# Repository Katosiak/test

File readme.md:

# System irygacji TytusPro

Aktualnie nasza firma “TytusPro”  zajmuję się realizacją projektu zautomatyzowanego systemu irygacyjnego stosowanego do nawadniania growboxa metodą deszczowania, czyli wytwarzania sztucznego deszczu poprzez deszczownicę. Do naszego urządzenia włączyliśmy 12 voltową pompę wody, oraz system rur aluminiowych. Nie zabrakło również lampy HPS która jest dopasowywana do danego growboxa w zależności od zapotrzebowania na moc (jeśli chodzi o małe pojemniki będzie to 250W). Sam growbox będzie wykonany z kawałków płyty wiórowej oraz listew. Woda jest dostarczana weżykiem do dysza zraszającego. Całe urządzenie funkcjonjuje pod zaprogramowanym zegarem który w zależności od cyklu dnia bądź nocy uruchamia światło jak i mechanizm zraszający naszą roślinę. Po całkowitej integracji urządzenia możesz udać się nawet na długie wakacje pozostawiając roślinę w naszych rękach. TytusPro dbamy o twoją zieleń!

## Plan działania 

# Elementy potrzebne do zbudowania naszego systemu wraz z ich parametrami

1. Pompa Wody
    - zasilanie 12V
    - wężyk o długości min. 150cm
    - średnica wylotu 1cm
    - wysokość podnoszenia wody wystarczy do 2,5/3 metrów
    - ciśnienie od 0,4 do 0,6 Bara

2. Oświetlenie – lampa HPS:
    - zależnie od warunków moc 250W lub 400W (bardziej 250W dla małego growboxa)

3. Wentylator:
    - około 30 wymian powietrza na godzinę
    - zasilanie 12V

4. Gniazdo e40 do lamp HPS

5. Przykładowe wymiary i materiały do budowy growboxa:]
    - 3 kawałki sklejki lub płyty wiórowej o wymiarach  1,21 metra x 2,42 metra i grubości  1,27 cm, przecięte na pół aby uzyskać sześć kawałków o wymiarach 1,21 m) x 1,21 m
    - 6 listew o szerokości 3,8 cm, grubości 3,8 cm i długości 2,43 m

6. Rury aluminiowe:]
    - średnica 1 cm
    - długość rur do 2/3 metrów

7. Kolanka aluminiowe:]
    - średnica 1 cm

8. Kable miedziane 2-żyłowe na napięcie 12V][]

9. Dysza do zraszania
    - średnica 1cm

# Schemat poglądowy systemu iregacyjnego

# Algorytm blokowy

# Opis fragmentów kodu

 - Czas i data uruchomienia

```C
RTC_Datetime_t datetime_start = {         
  .year = 23,
  .month = 02,
  .month_day = 03,                        
  .hour = 16,
  .minute = 00,
  .second = 00
};
```
- Zadeklarowane zdarzenia

```C
typedef enum {                          
	EVENT_Enable_Sun,
	EVENT_Enable_Water,
	EVENT_Enable_Air,
	EVENT_Disable_Sun,
	EVENT_Disable_Water,
	EVENT_Disable_Air,
} Event_e;
```
- Tablica alarmów, którą ustawiamy przed programowaniem urządzenia. Alarmy mają następować po sobie.

```C
 Alarm_t alarm_array[ALARM_COUNT] = {         
		{ .event = EVENT_Enable_Sun, .alarm = { .day_mask = true, .hour = 8, .minute = 0, .second = 0 } },
		{ .event = EVENT_Enable_Air, .alarm = { .day_mask = true, .hour = 12, .minute = 0, .second = 0 } },
		{ .event = EVENT_Enable_Water, .alarm = { .day_mask = true, .hour = 15, .minute = 0, .second = 0 } },
		{ .event = EVENT_Disable_Water, .alarm = { .day_mask = true, .hour = 15, .minute = 3, .second = 0 } },
		{ .event = EVENT_Disable_Air, .alarm = { .day_mask = true, .hour = 18, .minute = 0, .second = 0 } },
		{ .event = EVENT_Disable_Sun, .alarm = { .day_mask = true, .hour = 22, .minute = 0, .second = 0 } }
};
```
- Pętla for sprawdzająca najbliższy alarm z tablicy (NIE DZIAŁA)

```C
 for (uint8_t i = 0; i < ALARM_COUNT; i++) {                
    if(datetime_start.hour >= alarm_array[i].alarm.hour &&
       datetime_start.minute >= alarm_array[i].alarm.minute &&
	   datetime_start.second >= alarm_array[i].alarm.second) {

        RTC_Alarm_A_Enable(&(alarm_array[i].alarm));
 ```
- Event świadczy o obsłudze danego alarmu    

```C
 while(1)
		  {
			if(RTC_Event_A()) {

				switch(alarm_array[alarm_now].event) {         
				  case EVENT_Enable_Sun:
					  //for enable sun
					  break;
				  case EVENT_Enable_Air:
					  //for enable air
					  break;
				  case EVENT_Enable_Water:
					  //for enable water
					  break;
				  case EVENT_Disable_Water:
				  	  //for disable water
					  break;
				  case EVENT_Disable_Air:
					  //for disable air
					  break;
				  case EVENT_Disable_Sun:
					  //for disable sun
				  	  break;

				}
```
- Zwiększamy alarm o jeden, jeżeli nasz alarm jest większy bądź równy to zaczynamy od początku.
```js

				alarm_now++;                      
				if(alarm_now >= ALARM_COUNT) alarm_now = 0;     
				RTC_Alarm_A_Enable(&(alarm_array[alarm_now].alarm));

			  __NOP();
			}
			__NOP();
		  }
		 }

  }
}
```
#  Co należy dodać w przyszłości?

- Poprawić pętle for

- Ustawić pod przyciskiem aktualny czas

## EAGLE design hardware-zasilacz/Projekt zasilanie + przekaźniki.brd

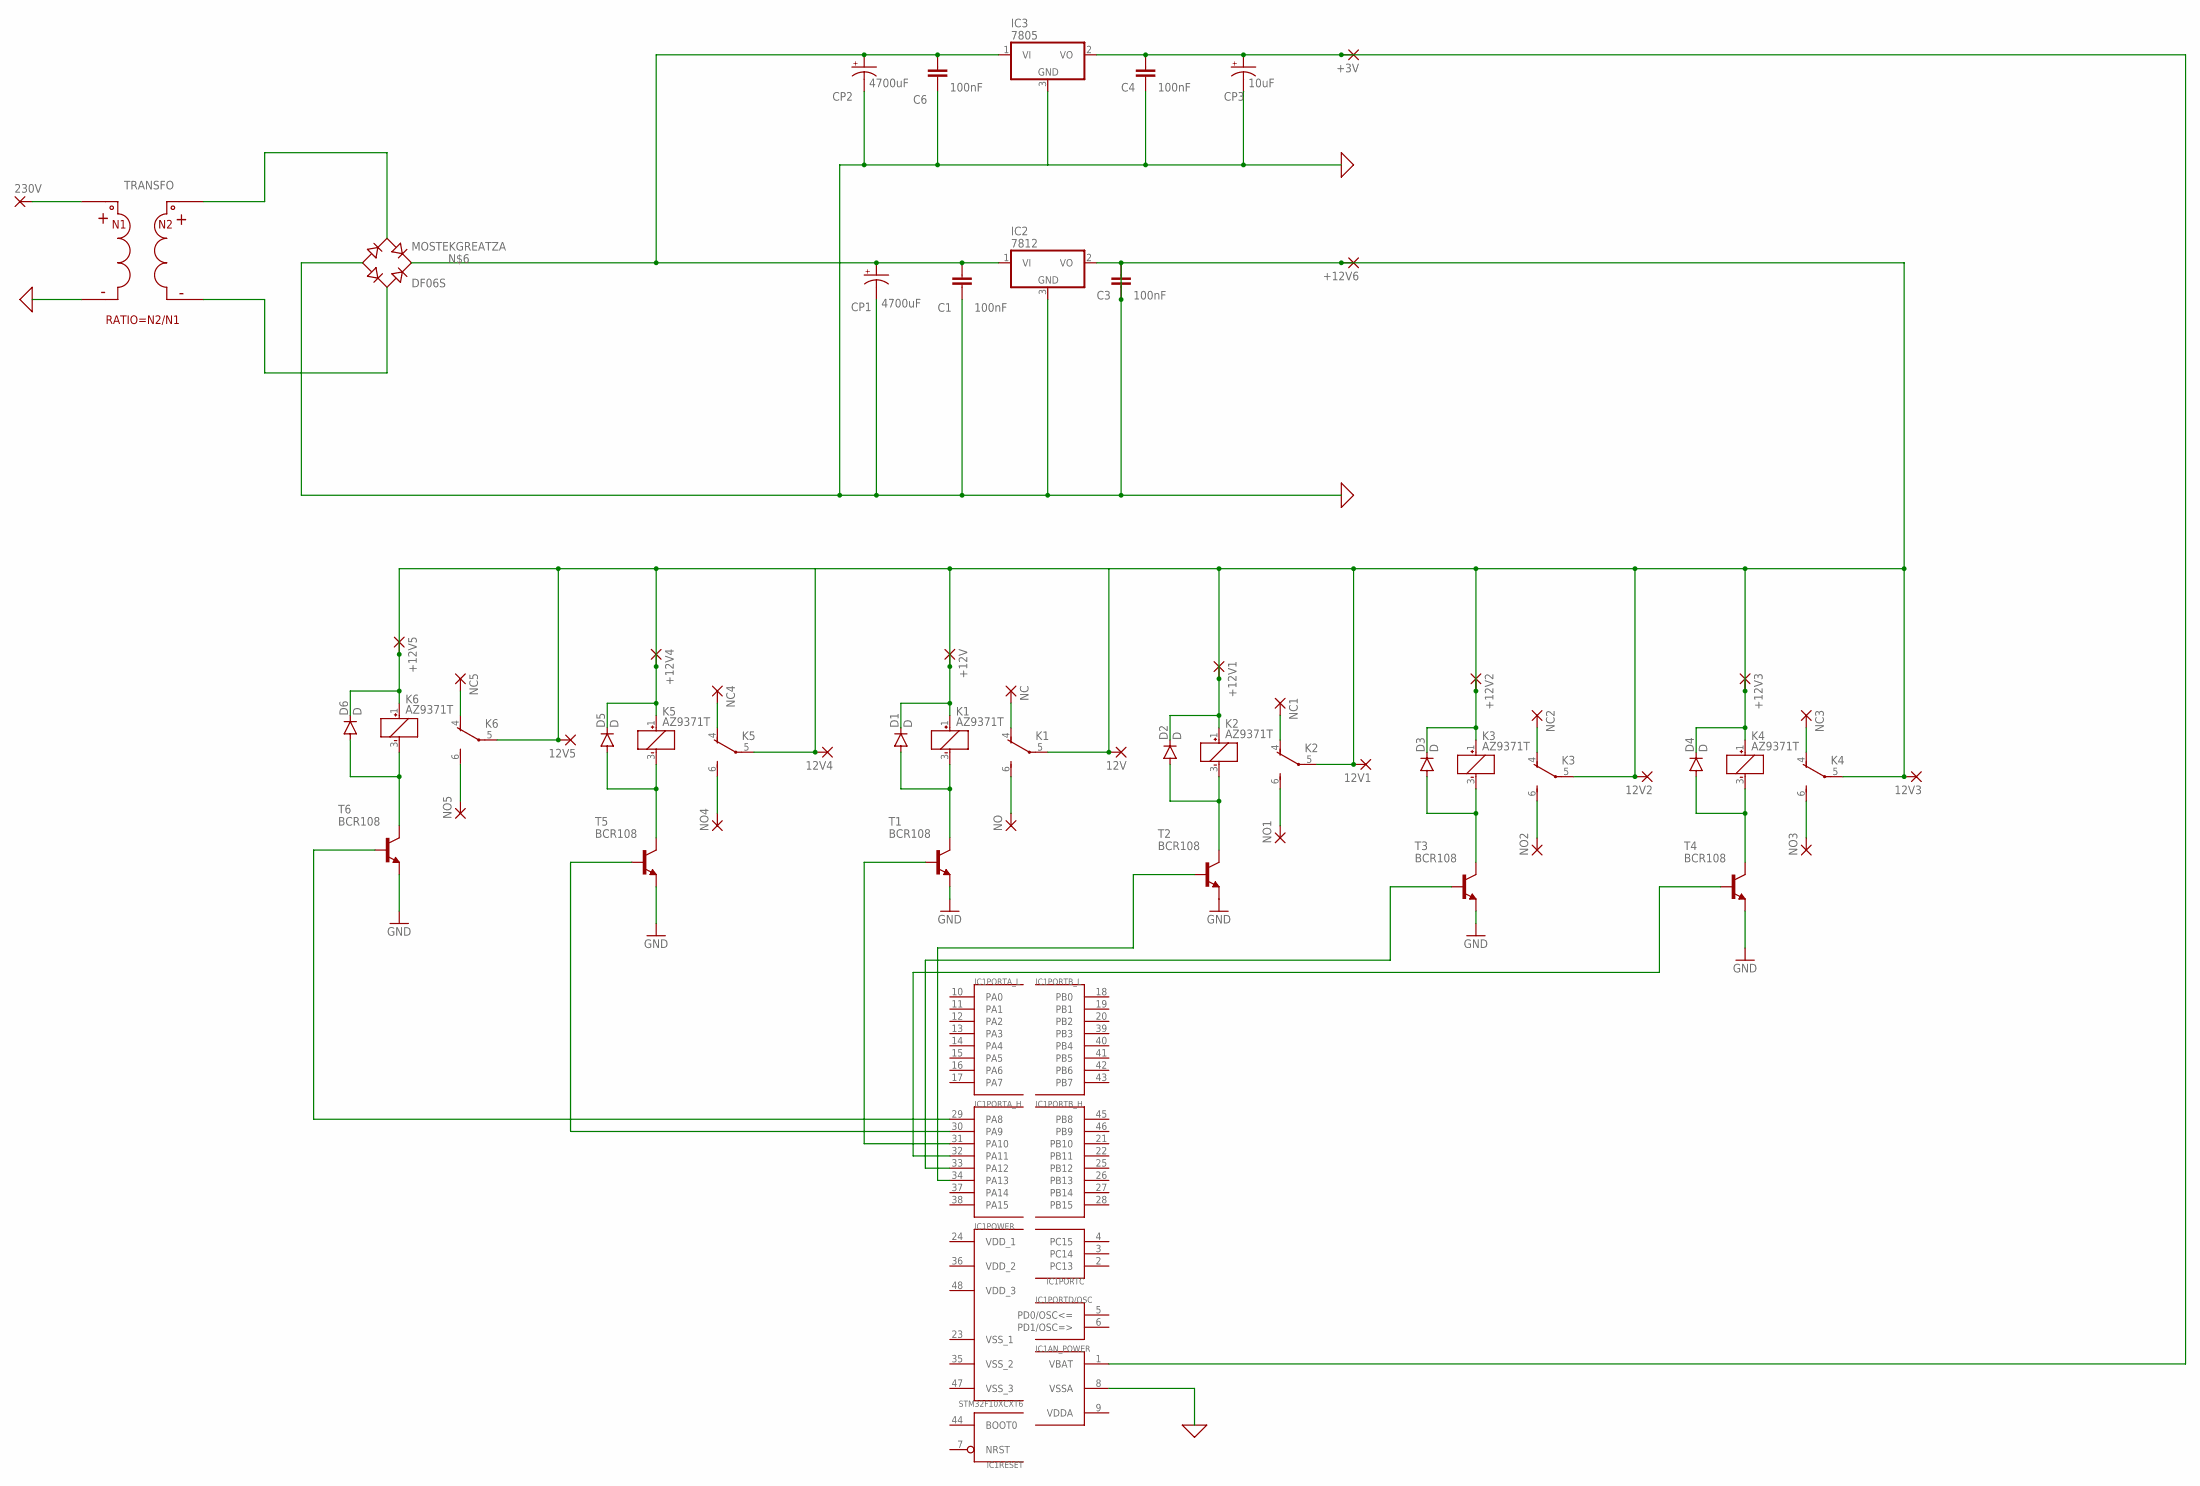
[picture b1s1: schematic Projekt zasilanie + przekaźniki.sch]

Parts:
12V, 12V1, 12V2, 12V3, 12V4, 12V5, 230V: SMD2; SMD1,27-2,54
+3V, +12V, +12V1, +12V2, +12V3, +12V4, +12V5, +12V6: SMD2; SMD1,27-2,54
CP1, CP2: 4700uF; 153CLV-0605
CP3: 10uF; 153CLV-0605
D1, D2, D3, D4, D5, D6: D; DO41-10
IC1: STM32F10XCXT6; TQFP48
IC2: 7812; TO252
IC3: 7805; TO252
K1, K2, K3, K4, K5, K6: AZ9371T; TK
MOSTEKGREATZA: DF06S; DFS
NC, NC1, NC2, NC3, NC4, NC5: SMD2; SMD1,27-2,54
NO, NO1, NO2, NO3, NO4, NO5: SMD2; SMD1,27-2,54
T1, T2, T3, T4, T5, T6: BCR108; TO5

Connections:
0: 12V.1, 12V1.1, 12V2.1, 12V3.1, 12V4.1, 12V5.1, +12V.1, +12V1.1, +12V2.1, +12V3.1, +12V4.1, +12V5.1, +12V6.1, CP1.-, CP2.-, CP3.-, D1.C, D2.C, D3.C, D4.C, D5.C, D6.C, IC1.8 (VSSA), IC2.2 (VO), IC2.3 (GND), IC3.3 (GND), K1.1 (+), K1.5, K2.1 (+), K2.5, K3.1 (+), K3.5, K4.1 (+), K4.5, K5.1 (+), K5.5, K6.1 (+), K6.5, MOSTEKGREATZA.-
GND: T1.1 (E), T2.1 (E), T3.1 (E), T4.1 (E), T5.1 (E), T6.1 (E)
unnamed: IC1.31 (PA10), T1.2 (B)
unnamed: D1.A, K1.3 (-), T1.3 (C)
unnamed: K1.6 (S), NO.1
unnamed: K1.4 (O), NC.1
unnamed: CP1.+, CP2.+, IC2.1 (VI), IC3.1 (VI), MOSTEKGREATZA.+
unnamed: IC1.34 (PA13), T2.2 (B)
unnamed: D2.A, K2.3 (-), T2.3 (C)
unnamed: K2.6 (S), NO1.1
unnamed: K2.4 (O), NC1.1
unnamed: IC1.33 (PA12), T3.2 (B)
unnamed: D3.A, K3.3 (-), T3.3 (C)
unnamed: K3.6 (S), NO2.1
unnamed: K3.4 (O), NC2.1
unnamed: IC1.32 (PA11), T4.2 (B)
unnamed: D4.A, K4.3 (-), T4.3 (C)
unnamed: K4.6 (S), NO3.1
unnamed: K4.4 (O), NC3.1
unnamed: IC1.30 (PA9), T5.2 (B)
unnamed: D5.A, K5.3 (-), T5.3 (C)
unnamed: K5.6 (S), NO4.1
unnamed: K5.4 (O), NC4.1
unnamed: IC1.29 (PA8), T6.2 (B)
unnamed: D6.A, K6.3 (-), T6.3 (C)
unnamed: K6.6 (S), NO5.1
unnamed: K6.4 (O), NC5.1
unnamed: +3V.1, CP3.+, IC1.1 (VBAT), IC3.2 (VO)
VDDA: IC1.9 (VDDA)
VDD_1: IC1.24 (VDD_1)
VDD_2: IC1.36 (VDD_2)
VDD_3: IC1.48 (VDD_3)
VSS_1: IC1.23 (VSS_1)
VSS_2: IC1.35 (VSS_2)
VSS_3: IC1.47 (VSS_3)

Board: 2 copper layers, 52 parts (0 on the bottom side), 28 nets, no tracks yet.

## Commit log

2023-02-03 TytusPro
